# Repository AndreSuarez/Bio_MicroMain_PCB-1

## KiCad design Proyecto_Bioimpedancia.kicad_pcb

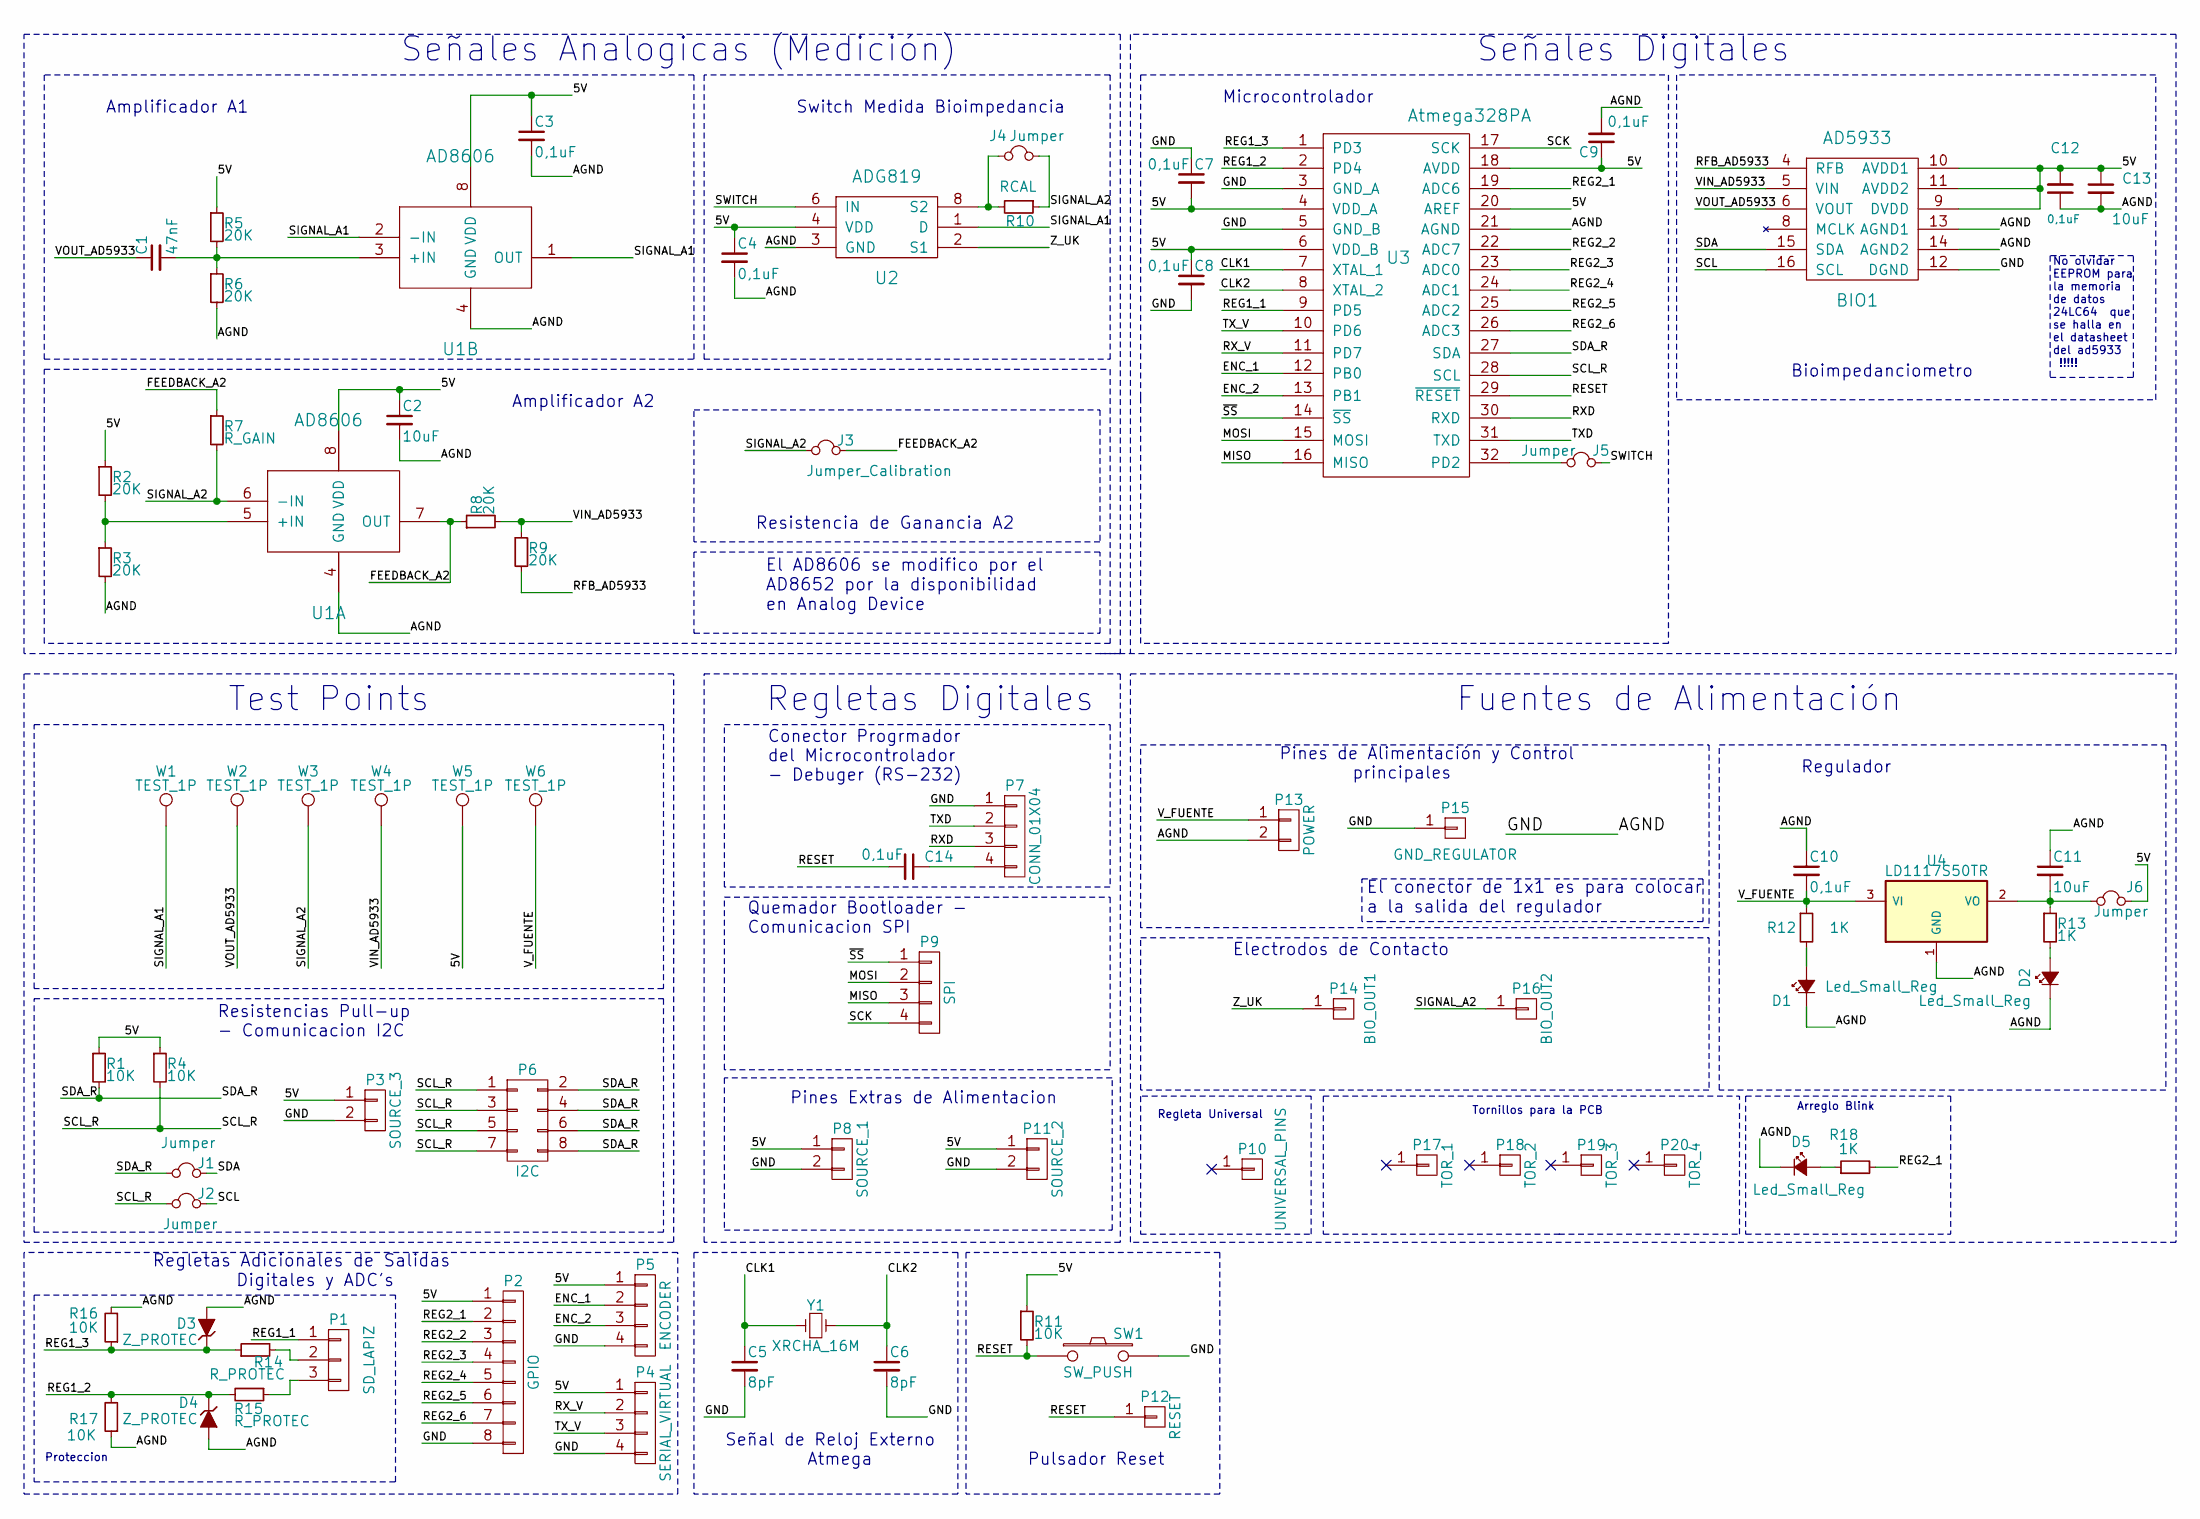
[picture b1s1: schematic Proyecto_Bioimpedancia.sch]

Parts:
BIO1: AD5933; SSOP-16_5.3x6.2mm_Pitch0.65mm
C1: 47nF; C_0805_HandSoldering
C2, C11, C13: 10uF; C_0805_HandSoldering
C3, C4, C7, C8, C9, C10, C12, C14: 0,1uF; C_0805_HandSoldering
C5, C6: 8pF; C_0402
D1, D2, D5: Led_Small_Reg; LED_0805
D3, D4: Z_PROTEC; D_DO-41_SOD81_P10.16mm_Horizontal
J1, J2, J4, J5, J6: Jumper; Pin_Header_Straight_1x02_Pitch2.54mm
J3: Jumper_Calibration; Pin_Header_Straight_1x02_Pitch2.54mm
P1: SD_LAPIZ; Socket_MOLEX-KK-RM3-96mm_Lock_3pin_straight
P2: GPIO; Socket_Strip_Straight_1x08_Pitch2.54mm
P3: SOURCE_3; Socket_MOLEX-KK-RM3-96mm_Lock_2pin_straight
P4: SERIAL_VIRTUAL; Socket_Strip_Straight_1x04_Pitch2.54mm
P5: ENCODER; Socket_Strip_Straight_1x04_Pitch2.54mm
P6: I2C; Socket_Strip_Straight_2x04_Pitch2.54mm
P7: CONN_01X04; Socket_Strip_Straight_1x04_Pitch2.54mm
P8: SOURCE_1; Socket_MOLEX-KK-RM3-96mm_Lock_2pin_straight
P9: SPI; Socket_Strip_Straight_1x04_Pitch2.54mm
P10: UNIVERSAL_PINS; Universal_Path_300_Pins
P11: SOURCE_2; Socket_MOLEX-KK-RM3-96mm_Lock_2pin_straight
P12: RESET; Socket_Strip_Straight_1x01_Pitch2.54mm
P13: POWER; Socket_MOLEX-KK-RM3-96mm_Lock_2pin_straight
P14: BIO_OUT1; SMA_THT_Jack_Straight
P15: GND_REGULATOR; Socket_Strip_Straight_1x01_Pitch2.54mm
P16: BIO_OUT2; SMA_THT_Jack_Straight
P17: TOR_1; MountingHole_3.2mm_M3_Pad_Via
P18: TOR_2; MountingHole_3.2mm_M3_Pad_Via
P19: TOR_3; MountingHole_3.2mm_M3_Pad_Via
P20: TOR_4; MountingHole_3.2mm_M3_Pad_Via
R1, R4, R11, R16, R17: 10K; R_0805_HandSoldering
R2, R3, R5, R6, R8, R9: 20K; R_0805_HandSoldering
R7: R_GAIN; R_0805_HandSoldering
R10: RCAL; R_0805_HandSoldering
R12, R13, R18: 1K; R_0805_HandSoldering
R14, R15: R_PROTEC; R_Axial_DIN0414_L11.9mm_D4.5mm_P20.32mm_Horizontal
SW1: SW_PUSH; KPT_1187B
U1: AD8606; SOIC-8_3.9x4.9mm_Pitch1.27mm
U2: ADG819; MSOP-8_3x3mm_Pitch0.65mm
U3: Atmega328PA; TQFP-32_7x7mm_Pitch0.8mm
U4: LD1117S50TR; SOT-223
W1, W2, W3, W4, W5, W6: TEST_1P; Measurement_Point_Round-TH_Small
Y1: XRCHA_16M; Crystal_SMD_XRCHA_Murata_Serie_W2,5mm_L2,0mm

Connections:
/5V: BIO1.9 (DVDD), BIO1.10 (AVDD1), BIO1.11 (AVDD2), C2.1, C3.1, C4.1, C7.2, C8.1, C9.1, C12.2, C13.1, J6.1, P2.1, P3.1, P4.1, P5.1, P8.1, P11.1, R1.1, R2.1, R4.1, R5.1, R11.1, U1.8 (VDD), U2.4 (VDD), U3.4 (VDD_A), U3.6 (VDD_B), U3.18 (AVDD), U3.20 (AREF), W5.1
/AGND: BIO1.12 (DGND), BIO1.13 (AGND1), BIO1.14 (AGND2), C2.2, C3.2, C4.2, C5.2, C6.2, C7.1, C8.2, C9.2, C10.1, C11.1, C12.1, C13.2, D1.1 (K), D2.1 (K), D3.2 (A), D4.2 (A), D5.1 (K), P2.8, P3.2, P4.4, P5.4, P7.1, P8.2, P11.2, P13.2, P15.1, R3.2, R6.2, R16.2, R17.1, SW1.2, U1.4 (GND), U2.3 (GND), U3.3 (GND_A), U3.5 (GND_B), U3.21 (AGND), U4.1 (GND)
/CLK1: C5.1, U3.7 (XTAL_1), Y1.1
/CLK2: C6.1, U3.8 (XTAL_2), Y1.2
/ENC_1: P5.2, U3.12 (PB0)
/ENC_2: P5.3, U3.13 (PB1)
/FEEDBACK_A2: J3.1, R7.1, R8.1, U1.7 (OUT)
/MISO: P9.3, U3.16 (MISO)
/MOSI: P9.2, U3.15 (MOSI)
/REG1_1: P1.1, U3.9 (PD5)
/REG1_2: D4.1 (K), R15.2, R17.2, U3.2 (PD4)
/REG1_3: D3.1 (K), R14.1, R16.1, U3.1 (PD3)
/REG2_1: P2.2, R18.2, U3.19 (ADC6)
/REG2_2: P2.3, U3.22 (ADC7)
/REG2_3: P2.4, U3.23 (ADC0)
/REG2_4: P2.5, U3.24 (ADC1)
/REG2_5: P2.6, U3.25 (ADC2)
/REG2_6: P2.7, U3.26 (ADC3)
/RESET: C14.2, P12.1, R11.2, SW1.1, U3.29 (~RESET)
/RFB_AD5933: BIO1.4 (RFB), R9.2
/RXD: P7.3, U3.30 (RXD)
/RX_V: P4.2, U3.11 (PD7)
/SCK: P9.4, U3.17 (SCK)
/SCL: BIO1.16 (SCL), J2.1
/SCL_R: J2.2, P6.1, P6.3, P6.5, P6.7, R4.2, U3.28 (SCL)
/SDA: BIO1.15 (SDA), J1.1
/SDA_R: J1.2, P6.2, P6.4, P6.6, P6.8, R1.2, U3.27 (SDA)
/SIGNAL_A1: U1.1 (OUT), U1.2 (-IN), U2.1 (D), W1.1
/SIGNAL_A2: J3.2, J4.1, P16.1, R7.2, R10.1, U1.6 (-IN), W3.1
/SWITCH: J5.1, U2.6 (IN)
/TXD: P7.2, U3.31 (TXD)
/TX_V: P4.3, U3.10 (PD6)
/VIN_AD5933: BIO1.5 (VIN), R8.2, R9.1, W4.1
/VOUT_AD5933: BIO1.6 (VOUT), C1.1, W2.1
/V_FUENTE: C10.2, P13.1, R12.1, U4.3 (VI), W6.1
/Z_UK: P14.1, U2.2 (S1)
/~SS: P9.1, U3.14 (~SS)
unnamed: C1.2, R5.2, R6.1, U1.3 (+IN)
unnamed: C11.2, J6.2, R13.1, U4.2 (VO)
unnamed: C14.1, P7.4
unnamed: D1.2 (A), R12.2
unnamed: D2.2 (A), R13.2
unnamed: D5.2 (A), R18.1
unnamed: J4.2, R10.2, U2.8 (S2)
unnamed: J5.2, U3.32 (PD2)
unnamed: P1.2, R14.2
unnamed: P1.3, R15.1
unnamed: R2.2, R3.1, U1.5 (+IN)

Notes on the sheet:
Señales Digitales
Fuentes de Alimentación
Regletas Digitales
Test Points
Señal de Reloj Externo Atmega
Pulsador Reset
Bioimpedanciometro
Microcontrolador
Amplificador A1
Amplificador A2
Switch Medida Bioimpedancia
Quemador Bootloader - Comunicacion SPI
Conector Progrmador del Microcontrolador - Debuger (RS-232)
Regulador
Pines de Alimentación y Control principales
Resistencias Pull-up - Comunicacion I2C
Señales Analogicas (Medición)
Electrodos de Contacto
Resistencia de Ganancia A2
No olvidar EEPROM para la memoria de datos 24LC64 que se halla en el datasheet del ad5933 !!!!!
El AD8606 se modifico por el AD8652 por la disponibilidad en Analog Device
Regletas Adicionales de Salidas Digitales y ADC's
El conector de 1x1 es para colocar a la salida del regulador
Pines Extras de Alimentacion
Proteccion
Regleta Universal
Tornillos para la PCB
Arreglo Blink

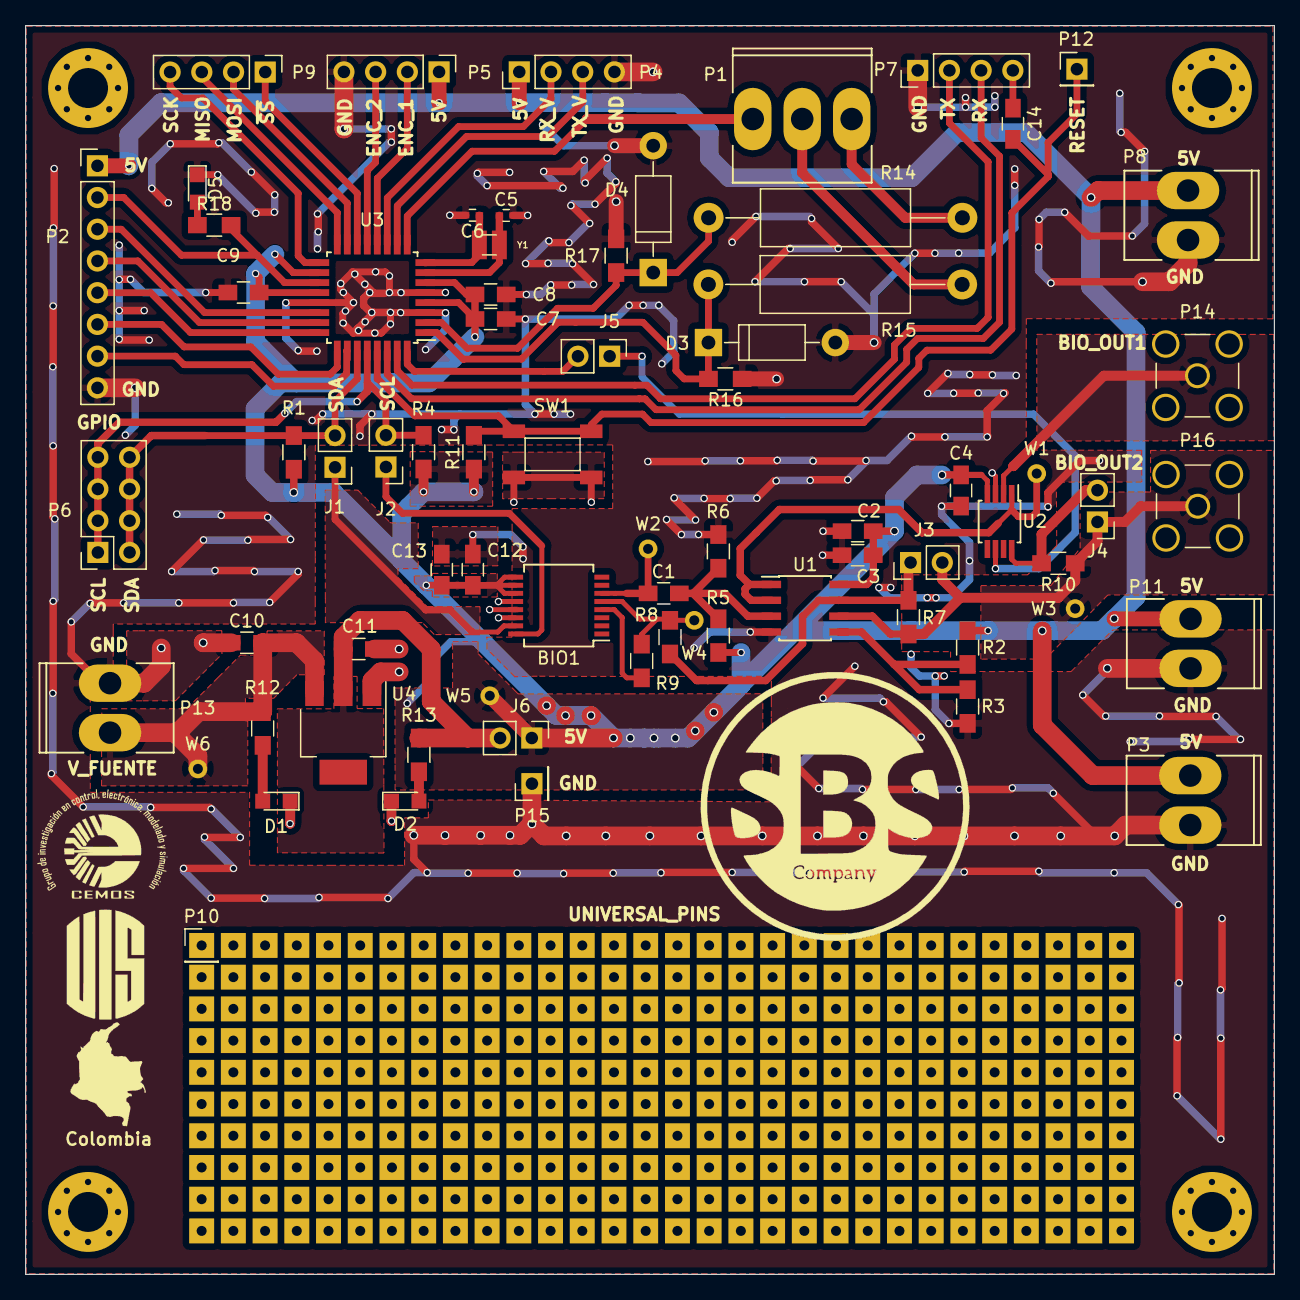
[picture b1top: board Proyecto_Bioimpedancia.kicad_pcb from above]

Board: 2 copper layers, 100.0 x 100.0 mm, 76 parts (0 on the bottom side), 48 nets.

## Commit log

2017-09-05 PCB Final_Bioimpedanciometro
    Aqui se realizaron los cambios previamente hablados y las correcciones
    necesarias
2017-09-28 PCB-1_Prototipo_1
2017-09-30 Cambio de limites de la PCB
2017-10-01 Cambio de nombre regleta SD_LAPIZ
2017-10-02 Cambio de clock
2017-10-02 Correcciones PCB BIO
2017-10-02 Conectores SMA actualizados
2017-10-02 PCB BIO mejorada con puertos I2C y capacitor para el puerto DTR del programador FTDI
2017-10-03 Revert "PCB BIO mejorada con puertos I2C y capacitor para el puerto DTR del programador FTDI"
    This reverts commit 0fb084b6cb4dcbd826a5771fbeb8258d6327cef0.
2017-10-03 PCB version final
2017-10-03 Regleta Universal Añadida
2017-10-03 Gerber generado
2017-10-04 Version para placa
2017-10-04 Led Prueba Blink Añadido
2017-10-04 Placa Actualizada
2017-10-05 Logos y Nombre de la Placa
2017-10-05 Vias de PCB
2017-10-05 Archivo .zip actualizado de Gerbers
2017-10-05 Planos de placa mejorados
2017-10-05 Capacitores de Cristal 0402 cambiados
2017-10-05 Archivo .zip Gerber actualizado
2017-10-05 Nombre de Colombia añadido
